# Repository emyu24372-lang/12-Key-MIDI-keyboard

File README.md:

# 12 Key MIDI keyboard
Here you will find the files for the MIDI keyboard.

I want to point out that some parts of the code may not work as expected.
Unfortunately, I haven't had the time to test it on a physical board yet.
Once I get the chance, I'll come back and update the code with a potentially better version.

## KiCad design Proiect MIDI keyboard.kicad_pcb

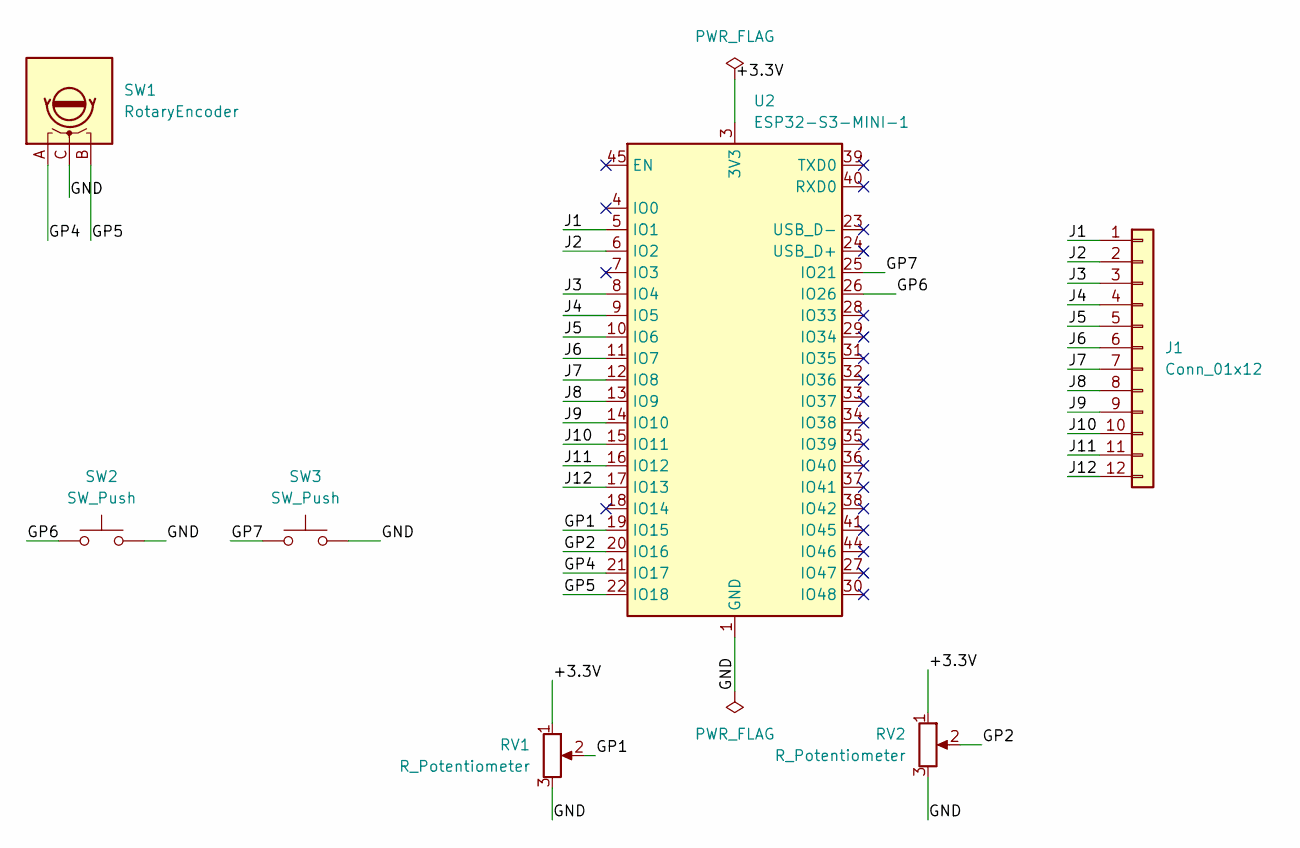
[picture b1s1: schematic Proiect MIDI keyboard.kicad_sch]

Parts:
J1: Conn_01x12; PinHeader_1x12_P2.54mm_Vertical
RV1, RV2: R_Potentiometer; Potentiometer_Bourns_PTA2043_Single_Slide
SW1: RotaryEncoder; RotaryEncoder_Alps_EC11E-Switch_Vertical_H20mm
SW2, SW3: SW_Push; SW_PUSH_6mm
U2: ESP32-S3-MINI-1; ESP32-S2-MINI-1

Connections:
/+3.3V: RV1.1, RV2.1, U2.3 (3V3)
/GND: RV1.3, RV2.3, SW1.C, SW2.2, SW3.2, U2.1 (GND), U2.2 (GND), U2.42 (GND), U2.43 (GND), U2.46 (GND), U2.47 (GND), U2.48 (GND), U2.49 (GND), U2.50 (GND), U2.51 (GND), U2.52 (GND), U2.53 (GND), U2.54 (GND), U2.55 (GND), U2.56 (GND), U2.57 (GND), U2.58 (GND), U2.59 (GND), U2.60 (GND), U2.61 (GND), U2.62 (GND), U2.63 (GND), U2.64 (GND), U2.65 (GND)
/GP1: RV1.2, U2.19 (IO15)
/GP2: RV2.2, U2.20 (IO16)
/GP4: SW1.A, U2.21 (IO17)
/GP5: SW1.B, U2.22 (IO18)
/GP6: SW2.1, U2.26 (IO26)
/GP7: SW3.1, U2.25 (IO21)
/J1: J1.1, U2.5 (IO1)
/J2: J1.2, U2.6 (IO2)
/J3: J1.3, U2.8 (IO4)
/J4: J1.4, U2.9 (IO5)
/J5: J1.5, U2.10 (IO6)
/J6: J1.6, U2.11 (IO7)
/J7: J1.7, U2.12 (IO8)
/J8: J1.8, U2.13 (IO9)
/J9: J1.9, U2.14 (IO10)
/J10: J1.10, U2.15 (IO11)
/J11: J1.11, U2.16 (IO12)
/J12: J1.12, U2.17 (IO13)

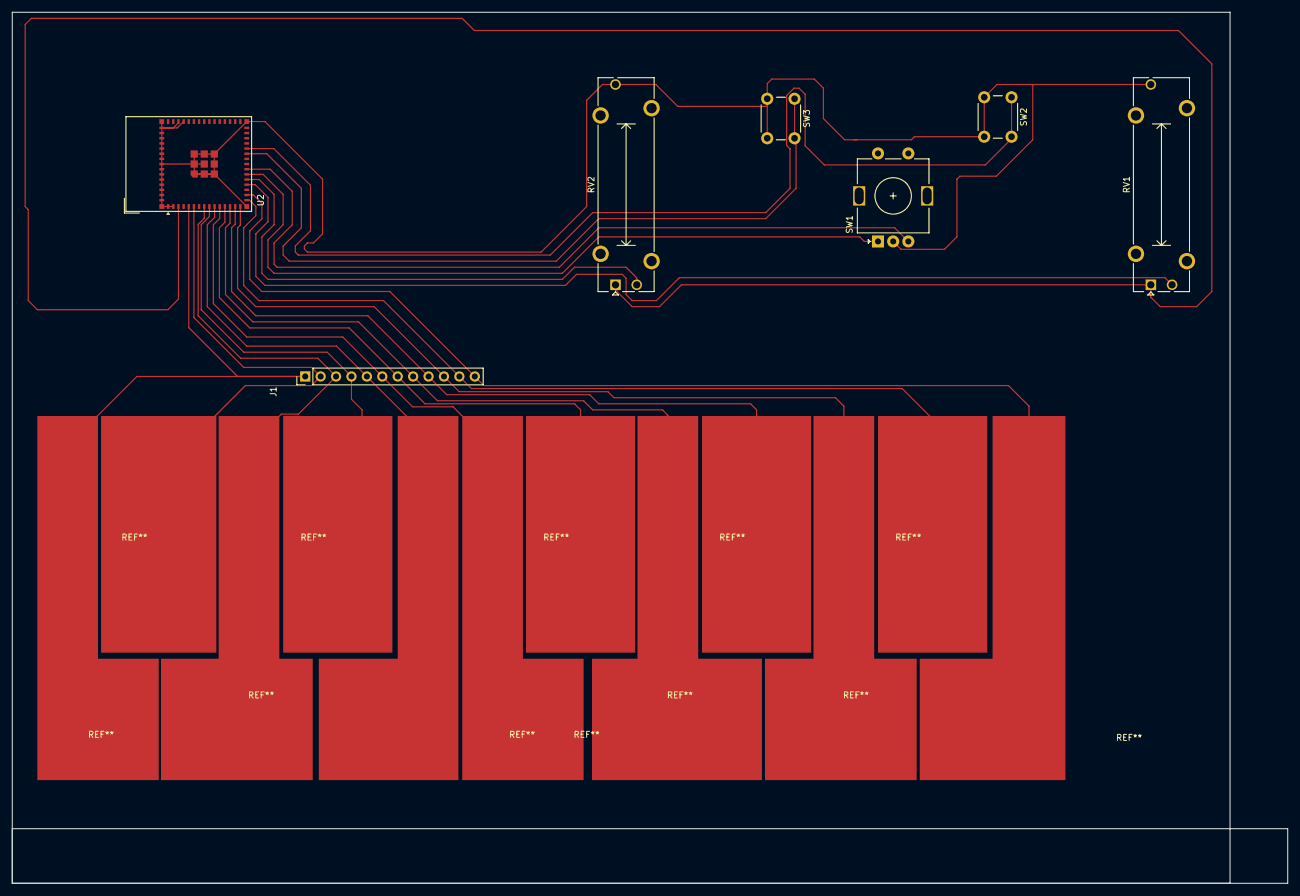
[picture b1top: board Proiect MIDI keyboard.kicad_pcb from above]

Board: 2 copper layers, 210.1 x 143.5 mm, 7 parts (0 on the bottom side), 20 nets.
